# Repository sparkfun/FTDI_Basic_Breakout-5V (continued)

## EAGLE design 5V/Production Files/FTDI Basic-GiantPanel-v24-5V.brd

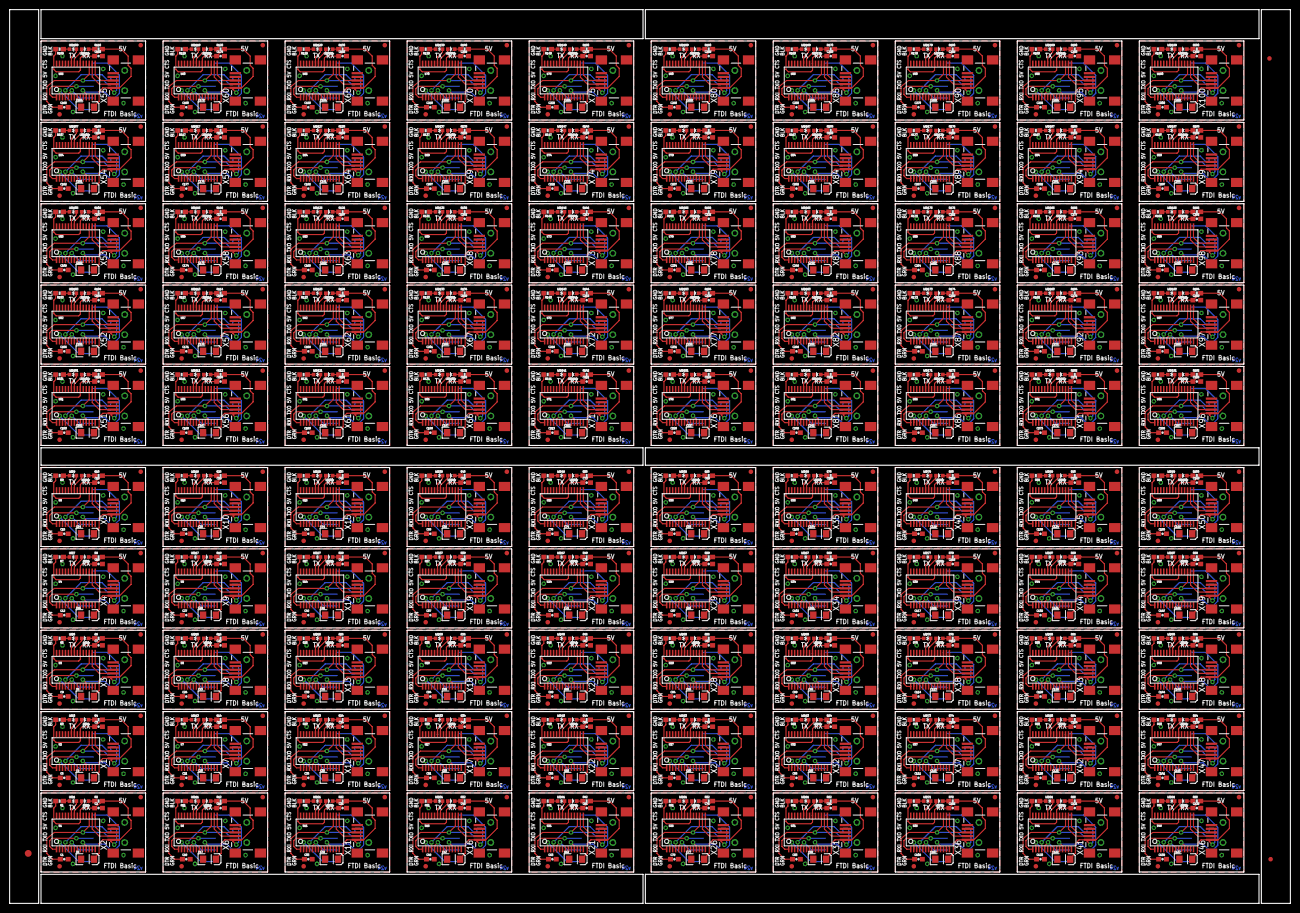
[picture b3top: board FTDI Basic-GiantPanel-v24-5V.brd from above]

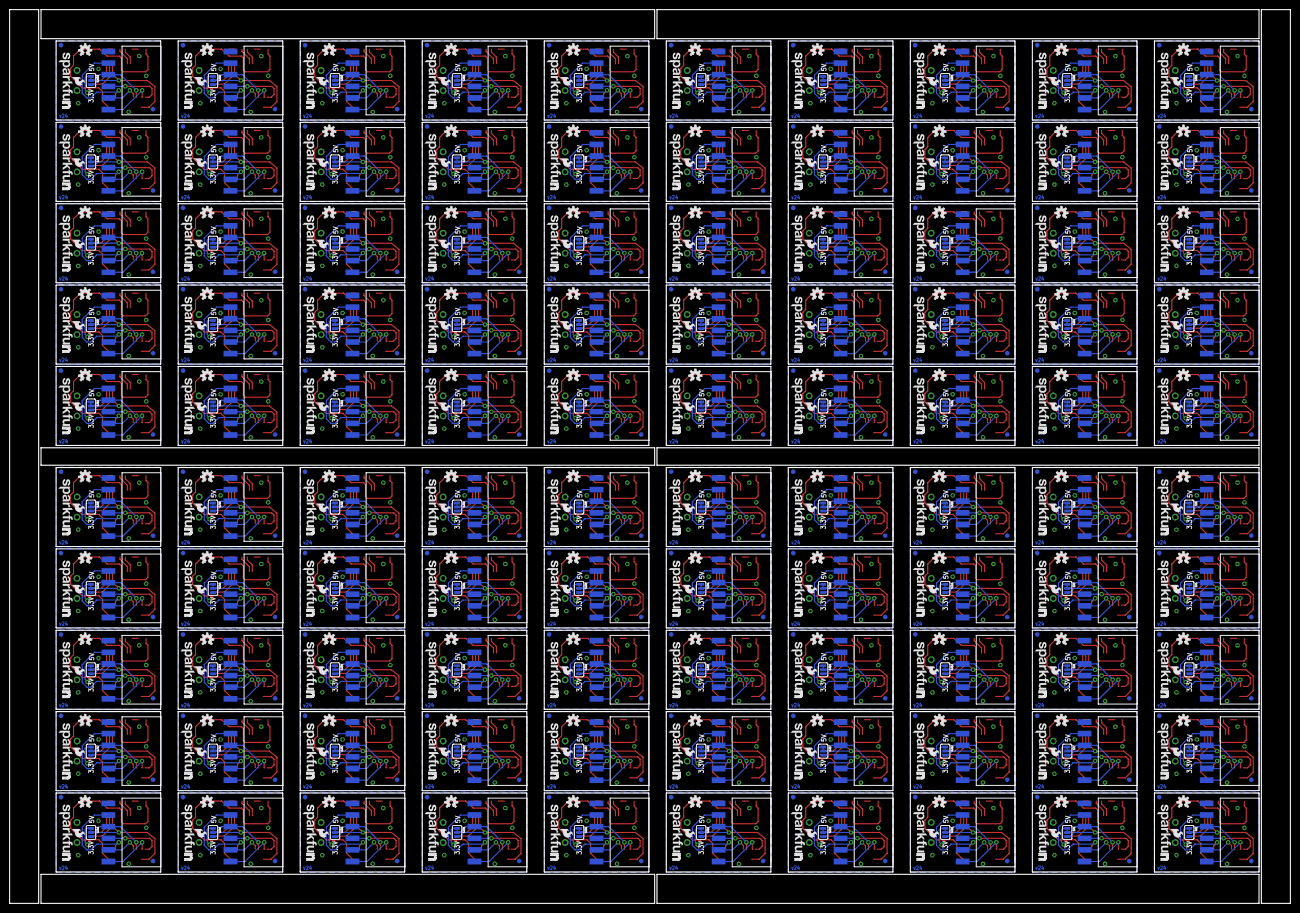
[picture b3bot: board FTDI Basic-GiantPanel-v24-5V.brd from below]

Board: 2 copper layers, 279.9 x 195.3 mm, 1803 parts (700 on the bottom side), 1400 nets.

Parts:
C1, C2, C3, C6, C7, C9, C10, C12, C13, C15, C16, C18, C19, C21, C22, C24, C25, C27, C28, C30, C31, C33, C34, C36, C37, C39, C40, C42, C43, C45, C46, C48, C49, C51, C52, C54, C55, C57, C58, C60, C61, C63, C64, C66, C67, C69, C70, C72, C73, C75, C76, C78, C79, C81, C82, C84, C85, C87, C88, C90, C91, C93, C94, C96, C97, C99, C100, C102, C103, C105, C106, C108, C109, C111, C112, C114, C115, C117, C118, C120, C121, C123, C124, C126, C127, C129, C130, C132, C133, C135, C136, C138, C139, C141, C142, C144, C145, C147, C148, C150, C151, C153, C154, C156, C157, C159, C160, C162, C163, C165, C166, C168, C169, C171, C172, C174, C175, C177, C178, C180, C181, C183, C184, C186, C187, C189, C190, C192, C193, C195, C196, C198, C199, C201, C202, C204, C205, C207, C208, C210, C211, C213, C214, C216, C217, C219, C220, C222, C223, C225, C226, C228, C229, C231, C232, C234, C235, C237, C238, C240, C241, C243, C244, C246, C247, C249, C250, C252, C253, C255, C256, C258, C259, C261, C262, C264, C265, C267, C268, C270, C271, C273, C274, C276, C277, C279, C280, C282, C283, C285, C286, C288, C289, C291, C292, C294, C295, C297, C298, C300: 0.1uF; 0603-CAP
C4, C5, C8, C11, C14, C17, C20, C23, C26, C29, C32, C35, C38, C41, C44, C47, C50, C53, C56, C59, C62, C65, C68, C71, C74, C77, C80, C83, C86, C89, C92, C95, C98, C101, C104, C107, C110, C113, C116, C119, C122, C125, C128, C131, C134, C137, C140, C143, C146, C149, C152, C155, C158, C161, C164, C167, C170, C173, C176, C179, C182, C185, C188, C191, C194, C197, C200, C203, C206, C209, C212, C215, C218, C221, C224, C227, C230, C233, C236, C239, C242, C245, C248, C251, C254, C257, C260, C263, C266, C269, C272, C275, C278, C281, C284, C287, C290, C293, C296, C299: 10uF; EIA3216
E$1: FIDUCIAL-1.5X3
E$6, E$16: FIDUCIAL-1X2
JP1, JP8, JP14, JP20, JP26, JP32, JP38, JP44, JP50, JP56, JP62, JP68, JP74, JP80, JP86, JP92, JP98, JP104, JP110, JP116, JP122, JP128, JP134, JP140, JP146, JP152, JP158, JP164, JP170, JP176, JP182, JP188, JP194, JP200, JP206, JP212, JP218, JP224, JP230, JP236, JP242, JP248, JP254, JP260, JP266, JP272, JP278, JP284, JP290, JP296, JP302, JP308, JP314, JP320, JP326, JP332, JP338, JP344, JP350, JP356, JP362, JP368, JP374, JP380, JP386, JP392, JP398, JP404, JP410, JP416, JP422, JP428, JP434, JP440, JP446, JP452, JP458, JP464, JP470, JP476, JP482, JP488, JP494, JP500, JP506, JP512, JP518, JP524, JP530, JP536, JP542, JP548, JP554, JP560, JP566, JP572, JP578, JP584, JP590, JP596: 1X06-SMD-FEMALE-V2
JP2, JP7, JP13, JP19, JP25, JP31, JP37, JP43, JP49, JP55, JP61, JP67, JP73, JP79, JP85, JP91, JP97, JP103, JP109, JP115, JP121, JP127, JP133, JP139, JP145, JP151, JP157, JP163, JP169, JP175, JP181, JP187, JP193, JP199, JP205, JP211, JP217, JP223, JP229, JP235, JP241, JP247, JP253, JP259, JP265, JP271, JP277, JP283, JP289, JP295, JP301, JP307, JP313, JP319, JP325, JP331, JP337, JP343, JP349, JP355, JP361, JP367, JP373, JP379, JP385, JP391, JP397, JP403, JP409, JP415, JP421, JP427, JP433, JP439, JP445, JP451, JP457, JP463, JP469, JP475, JP481, JP487, JP493, JP499, JP505, JP511, JP517, JP523, JP529, JP535, JP541, JP547, JP553, JP559, JP565, JP571, JP577, JP583, JP589, JP595: LOGO-SFESK; SFE-LOGO-FLAME
JP3, JP4, JP5, JP6, JP9, JP10, JP11, JP12, JP15, JP16, JP17, JP18, JP21, JP22, JP23, JP24, JP27, JP28, JP29, JP30, JP33, JP34, JP35, JP36, JP39, JP40, JP41, JP42, JP45, JP46, JP47, JP48, JP51, JP52, JP53, JP54, JP57, JP58, JP59, JP60, JP63, JP64, JP65, JP66, JP69, JP70, JP71, JP72, JP75, JP76, JP77, JP78, JP81, JP82, JP83, JP84, JP87, JP88, JP89, JP90, JP93, JP94, JP95, JP96, JP99, JP100, JP101, JP102, JP105, JP106, JP107, JP108, JP111, JP112, JP113, JP114, JP117, JP118, JP119, JP120, JP123, JP124, JP125, JP126, JP129, JP130, JP131, JP132, JP135, JP136, JP137, JP138, JP141, JP142, JP143, JP144, JP147, JP148, JP149, JP150, JP153, JP154, JP155, JP156, JP159, JP160, JP161, JP162, JP165, JP166, JP167, JP168, JP171, JP172, JP173, JP174, JP177, JP178, JP179, JP180, JP183, JP184, JP185, JP186, JP189, JP190, JP191, JP192, JP195, JP196, JP197, JP198, JP201, JP202, JP203, JP204, JP207, JP208, JP209, JP210, JP213, JP214, JP215, JP216, JP219, JP220, JP221, JP222, JP225, JP226, JP227, JP228, JP231, JP232, JP233, JP234, JP237, JP238, JP239, JP240, JP243, JP244, JP245, JP246, JP249, JP250, JP251, JP252, JP255, JP256, JP257, JP258, JP261, JP262, JP263, JP264, JP267, JP268, JP269, JP270, JP273, JP274, JP275, JP276, JP279, JP280, JP281, JP282, JP285, JP286, JP287, JP288, JP291, JP292, JP293, JP294, JP297, JP298, JP299, JP300, JP303, JP304, JP305, JP306, JP309, JP310, JP311, JP312, JP315, JP316, JP317, JP318, JP321, JP322, JP323, JP324, JP327, JP328, JP329, JP330, JP333, JP334, JP335, JP336, JP339, JP340, JP341, JP342, JP345, JP346, JP347, JP348, JP351, JP352, JP353, JP354, JP357, JP358, JP359, JP360, JP363, JP364, JP365, JP366, JP369, JP370, JP371, JP372, JP375, JP376, JP377, JP378, JP381, JP382, JP383, JP384, JP387, JP388, JP389, JP390, JP393, JP394, JP395, JP396, JP399, JP400, JP401, JP402, JP405, JP406, JP407, JP408, JP411, JP412, JP413, JP414, JP417, JP418, JP419, JP420, JP423, JP424, JP425, JP426, JP429, JP430, JP431, JP432, JP435, JP436, JP437, JP438, JP441, JP442, JP443, JP444, JP447, JP448, JP449, JP450, JP453, JP454, JP455, JP456, JP459, JP460, JP461, JP462, JP465, JP466, JP467, JP468, JP471, JP472, JP473, JP474, JP477, JP478, JP479, JP480, JP483, JP484, JP485, JP486, JP489, JP490, JP491, JP492, JP495, JP496, JP497, JP498, JP501, JP502, JP503, JP504, JP507, JP508, JP509, JP510, JP513, JP514, JP515, JP516, JP519, JP520, JP521, JP522, JP525, JP526, JP527, JP528, JP531, JP532, JP533, JP534, JP537, JP538, JP539, JP540, JP543, JP544, JP545, JP546, JP549, JP550, JP551, JP552, JP555, JP556, JP557, JP558, JP561, JP562, JP563, JP564, JP567, JP568, JP569, JP570, JP573, JP574, JP575, JP576, JP579, JP580, JP581, JP582, JP585, JP586, JP587, JP588, JP591, JP592, JP593, JP594, JP597, JP598, JP599, JP600: FIDUCIAL1X2; FIDUCIAL-1X2
LED1, LED3, LED5, LED7, LED9, LED11, LED13, LED15, LED17, LED19, LED21, LED23, LED25, LED27, LED29, LED31, LED33, LED35, LED37, LED39, LED41, LED43, LED45, LED47, LED49, LED51, LED53, LED55, LED57, LED59, LED61, LED63, LED65, LED67, LED69, LED71, LED73, LED75, LED77, LED79, LED81, LED83, LED85, LED87, LED89, LED91, LED93, LED95, LED97, LED99, LED101, LED103, LED105, LED107, LED109, LED111, LED113, LED115, LED117, LED119, LED121, LED123, LED125, LED127, LED129, LED131, LED133, LED135, LED137, LED139, LED141, LED143, LED145, LED147, LED149, LED151, LED153, LED155, LED157, LED159, LED161, LED163, LED165, LED167, LED169, LED171, LED173, LED175, LED177, LED179, LED181, LED183, LED185, LED187, LED189, LED191, LED193, LED195, LED197, LED199: Red; LED-0603
LED2, LED4, LED6, LED8, LED10, LED12, LED14, LED16, LED18, LED20, LED22, LED24, LED26, LED28, LED30, LED32, LED34, LED36, LED38, LED40, LED42, LED44, LED46, LED48, LED50, LED52, LED54, LED56, LED58, LED60, LED62, LED64, LED66, LED68, LED70, LED72, LED74, LED76, LED78, LED80, LED82, LED84, LED86, LED88, LED90, LED92, LED94, LED96, LED98, LED100, LED102, LED104, LED106, LED108, LED110, LED112, LED114, LED116, LED118, LED120, LED122, LED124, LED126, LED128, LED130, LED132, LED134, LED136, LED138, LED140, LED142, LED144, LED146, LED148, LED150, LED152, LED154, LED156, LED158, LED160, LED162, LED164, LED166, LED168, LED170, LED172, LED174, LED176, LED178, LED180, LED182, LED184, LED186, LED188, LED190, LED192, LED194, LED196, LED198, LED200: Green; LED-0603
LOGO1, LOGO2, LOGO3, LOGO4, LOGO5, LOGO6, LOGO7, LOGO8, LOGO9, LOGO10, LOGO11, LOGO12, LOGO13, LOGO14, LOGO15, LOGO16, LOGO17, LOGO18, LOGO19, LOGO20, LOGO21, LOGO22, LOGO23, LOGO24, LOGO25, LOGO26, LOGO27, LOGO28, LOGO29, LOGO30, LOGO31, LOGO32, LOGO33, LOGO34, LOGO35, LOGO36, LOGO37, LOGO38, LOGO39, LOGO40, LOGO41, LOGO42, LOGO43, LOGO44, LOGO45, LOGO46, LOGO47, LOGO48, LOGO49, LOGO50, LOGO51, LOGO52, LOGO53, LOGO54, LOGO55, LOGO56, LOGO57, LOGO58, LOGO59, LOGO60, LOGO61, LOGO62, LOGO63, LOGO64, LOGO65, LOGO66, LOGO67, LOGO68, LOGO69, LOGO70, LOGO71, LOGO72, LOGO73, LOGO74, LOGO75, LOGO76, LOGO77, LOGO78, LOGO79, LOGO80, LOGO81, LOGO82, LOGO83, LOGO84, LOGO85, LOGO86, LOGO87, LOGO88, LOGO89, LOGO90, LOGO91, LOGO92, LOGO93, LOGO94, LOGO95, LOGO96, LOGO97, LOGO98, LOGO99, LOGO100: OSHW-LOGOS; OSHW-LOGO-S
R1, R2, R3, R4, R5, R6, R7, R8, R9, R10, R11, R12, R13, R14, R15, R16, R17, R18, R19, R20, R21, R22, R23, R24, R25, R26, R27, R28, R29, R30, R31, R32, R33, R34, R35, R36, R37, R38, R39, R40, R41, R42, R43, R44, R45, R46, R47, R48, R49, R50, R51, R52, R53, R54, R55, R56, R57, R58, R59, R60, R61, R62, R63, R64, R65, R66, R67, R68, R69, R70, R71, R72, R73, R74, R75, R76, R77, R78, R79, R80, R81, R82, R83, R84, R85, R86, R87, R88, R89, R90, R91, R92, R93, R94, R95, R96, R97, R98, R99, R100, R101, R102, R103, R104, R105, R106, R107, R108, R109, R110, R111, R112, R113, R114, R115, R116, R117, R118, R119, R120, R121, R122, R123, R124, R125, R126, R127, R128, R129, R130, R131, R132, R133, R134, R135, R136, R137, R138, R139, R140, R141, R142, R143, R144, R145, R146, R147, R148, R149, R150, R151, R152, R153, R154, R155, R156, R157, R158, R159, R160, R161, R162, R163, R164, R165, R166, R167, R168, R169, R170, R171, R172, R173, R174, R175, R176, R177, R178, R179, R180, R181, R182, R183, R184, R185, R186, R187, R188, R189, R190, R191, R192, R193, R194, R195, R196, R197, R198, R199, R200: 1K; 0603-RES
SJ1, SJ2, SJ3, SJ4, SJ5, SJ6, SJ7, SJ8, SJ9, SJ10, SJ11, SJ12, SJ13, SJ14, SJ15, SJ16, SJ17, SJ18, SJ19, SJ20, SJ21, SJ22, SJ23, SJ24, SJ25, SJ26, SJ27, SJ28, SJ29, SJ30, SJ31, SJ32, SJ33, SJ34, SJ35, SJ36, SJ37, SJ38, SJ39, SJ40, SJ41, SJ42, SJ43, SJ44, SJ45, SJ46, SJ47, SJ48, SJ49, SJ50, SJ51, SJ52, SJ53, SJ54, SJ55, SJ56, SJ57, SJ58, SJ59, SJ60, SJ61, SJ62, SJ63, SJ64, SJ65, SJ66, SJ67, SJ68, SJ69, SJ70, SJ71, SJ72, SJ73, SJ74, SJ75, SJ76, SJ77, SJ78, SJ79, SJ80, SJ81, SJ82, SJ83, SJ84, SJ85, SJ86, SJ87, SJ88, SJ89, SJ90, SJ91, SJ92, SJ93, SJ94, SJ95, SJ96, SJ97, SJ98, SJ99, SJ100: SJ_3
U1, U2, U3, U4, U5, U6, U7, U8, U9, U10, U11, U12, U13, U14, U15, U16, U17, U18, U19, U20, U21, U22, U23, U24, U25, U26, U27, U28, U29, U30, U31, U32, U33, U34, U35, U36, U37, U38, U39, U40, U41, U42, U43, U44, U45, U46, U47, U48, U49, U50, U51, U52, U53, U54, U55, U56, U57, U58, U59, U60, U61, U62, U63, U64, U65, U66, U67, U68, U69, U70, U71, U72, U73, U74, U75, U76, U77, U78, U79, U80, U81, U82, U83, U84, U85, U86, U87, U88, U89, U90, U91, U92, U93, U94, U95, U96, U97, U98, U99, U100: FT232RLSSOP; SSOP28DB
U$1, U$2, U$3, U$4, U$5, U$6, U$7, U$8, U$9, U$10, U$11, U$12, U$13, U$14, U$15, U$16, U$17, U$18, U$19, U$20, U$21, U$22, U$23, U$24, U$25, U$26, U$27, U$28, U$29, U$30, U$31, U$32, U$33, U$34, U$35, U$36, U$37, U$38, U$39, U$40, U$41, U$42, U$43, U$44, U$45, U$46, U$47, U$48, U$49, U$50, U$51, U$52, U$53, U$54, U$55, U$56, U$57, U$58, U$59, U$60, U$61, U$62, U$63, U$64, U$65, U$66, U$67, U$68, U$69, U$70, U$71, U$72, U$73, U$74, U$75, U$76, U$77, U$78, U$79, U$80, U$81, U$82, U$83, U$84, U$85, U$86, U$87, U$88, U$89, U$90, U$91, U$92, U$93, U$94, U$95, U$96, U$97, U$98, U$99, U$100: LOGO-SFENW2; SFE-NEW-WEB
X1, X2, X3, X4, X5, X6, X7, X8, X9, X10, X11, X12, X13, X14, X15, X16, X17, X18, X19, X20, X21, X22, X23, X24, X25, X26, X27, X28, X29, X30, X31, X32, X33, X34, X35, X36, X37, X38, X39, X40, X41, X42, X43, X44, X45, X46, X47, X48, X49, X50, X51, X52, X53, X54, X55, X56, X57, X58, X59, X60, X61, X62, X63, X64, X65, X66, X67, X68, X69, X70, X71, X72, X73, X74, X75, X76, X77, X78, X79, X80, X81, X82, X83, X84, X85, X86, X87, X88, X89, X90, X91, X92, X93, X94, X95, X96, X97, X98, X99, X100: USB-SMD-NS; USB-MINIB-NOSTOP

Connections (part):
3.3V: C1.1, SJ2.3, U1.17
3.3V1: C6.1, SJ1.3, U2.17
3.3V2: C9.1, SJ3.3, U3.17
3.3V3: C12.1, SJ4.3, U4.17
3.3V4: C15.1, SJ5.3, U5.17
3.3V5: C18.1, SJ6.3, U6.17
3.3V6: C21.1, SJ7.3, U7.17
3.3V7: C24.1, SJ8.3, U8.17
3.3V8: C27.1, SJ9.3, U9.17
3.3V9: C30.1, SJ10.3, U10.17
3.3V10: C33.1, SJ11.3, U11.17
3.3V11: C36.1, SJ12.3, U12.17
3.3V12: C39.1, SJ13.3, U13.17
3.3V13: C42.1, SJ14.3, U14.17
3.3V14: C45.1, SJ15.3, U15.17
3.3V15: C48.1, SJ16.3, U16.17
3.3V16: C51.1, SJ17.3, U17.17
3.3V17: C54.1, SJ18.3, U18.17
3.3V18: C57.1, SJ19.3, U19.17
3.3V19: C60.1, SJ20.3, U20.17
3.3V20: C63.1, SJ21.3, U21.17
3.3V21: C66.1, SJ22.3, U22.17
3.3V22: C69.1, SJ23.3, U23.17
3.3V23: C72.1, SJ24.3, U24.17
3.3V24: C75.1, SJ25.3, U25.17
3.3V25: C78.1, SJ26.3, U26.17
3.3V26: C81.1, SJ27.3, U27.17
3.3V27: C84.1, SJ28.3, U28.17
3.3V28: C87.1, SJ29.3, U29.17
3.3V29: C90.1, SJ30.3, U30.17
3.3V30: C93.1, SJ31.3, U31.17
3.3V31: C96.1, SJ32.3, U32.17
3.3V32: C99.1, SJ33.3, U33.17
3.3V33: C102.1, SJ34.3, U34.17
3.3V34: C105.1, SJ35.3, U35.17
3.3V35: C108.1, SJ36.3, U36.17
3.3V36: C111.1, SJ37.3, U37.17
3.3V37: C114.1, SJ38.3, U38.17
3.3V38: C117.1, SJ39.3, U39.17
3.3V39: C120.1, SJ40.3, U40.17
3.3V40: C123.1, SJ41.3, U41.17
3.3V41: C126.1, SJ42.3, U42.17
3.3V42: C129.1, SJ43.3, U43.17
3.3V43: C132.1, SJ44.3, U44.17
3.3V44: C135.1, SJ45.3, U45.17
3.3V45: C138.1, SJ46.3, U46.17
3.3V46: C141.1, SJ47.3, U47.17
3.3V47: C144.1, SJ48.3, U48.17
3.3V48: C147.1, SJ49.3, U49.17
3.3V49: C150.1, SJ50.3, U50.17
3.3V50: C153.1, SJ51.3, U51.17
3.3V51: C156.1, SJ52.3, U52.17
3.3V52: C159.1, SJ53.3, U53.17
3.3V53: C162.1, SJ54.3, U54.17
3.3V54: C165.1, SJ55.3, U55.17
3.3V55: C168.1, SJ56.3, U56.17
3.3V56: C171.1, SJ57.3, U57.17
3.3V57: C174.1, SJ58.3, U58.17
3.3V58: C177.1, SJ59.3, U59.17
3.3V59: C180.1, SJ60.3, U60.17
3.3V60: C183.1, SJ61.3, U61.17
3.3V61: C186.1, SJ62.3, U62.17
3.3V62: C189.1, SJ63.3, U63.17
3.3V63: C192.1, SJ64.3, U64.17
3.3V64: C195.1, SJ65.3, U65.17
3.3V65: C198.1, SJ66.3, U66.17
3.3V66: C201.1, SJ67.3, U67.17
3.3V67: C204.1, SJ68.3, U68.17
3.3V68: C207.1, SJ69.3, U69.17
3.3V69: C210.1, SJ70.3, U70.17
3.3V70: C213.1, SJ71.3, U71.17
3.3V71: C216.1, SJ72.3, U72.17
3.3V72: C219.1, SJ73.3, U73.17
3.3V73: C222.1, SJ74.3, U74.17
3.3V74: C225.1, SJ75.3, U75.17
3.3V75: C228.1, SJ76.3, U76.17
3.3V76: C231.1, SJ77.3, U77.17
3.3V77: C234.1, SJ78.3, U78.17
3.3V78: C237.1, SJ79.3, U79.17
3.3V79: C240.1, SJ80.3, U80.17
3.3V80: C243.1, SJ81.3, U81.17
3.3V81: C246.1, SJ82.3, U82.17
3.3V82: C249.1, SJ83.3, U83.17
3.3V83: C252.1, SJ84.3, U84.17
3.3V84: C255.1, SJ85.3, U85.17
3.3V85: C258.1, SJ86.3, U86.17
3.3V86: C261.1, SJ87.3, U87.17
3.3V87: C264.1, SJ88.3, U88.17
3.3V88: C267.1, SJ89.3, U89.17
3.3V89: C270.1, SJ90.3, U90.17
3.3V90: C273.1, SJ91.3, U91.17
3.3V91: C276.1, SJ92.3, U92.17
3.3V92: C279.1, SJ93.3, U93.17
3.3V93: C282.1, SJ94.3, U94.17
3.3V94: C285.1, SJ95.3, U95.17
3.3V95: C288.1, SJ96.3, U96.17
3.3V96: C291.1, SJ97.3, U97.17
3.3V97: C294.1, SJ98.3, U98.17
3.3V98: C297.1, SJ99.3, U99.17
3.3V99: C300.1, SJ100.3, U100.17
5V: C2.1, C5.A, R1.2, R2.2, SJ2.1, U1.20, X2.VBUS
5V1: C3.1, C4.A, R3.2, R4.2, SJ1.1, U2.20, X1.VBUS
5V2: C7.1, C8.A, R5.2, R6.2, SJ3.1, U3.20, X3.VBUS
5V3: C10.1, C11.A, R7.2, R8.2, SJ4.1, U4.20, X4.VBUS
5V4: C13.1, C14.A, R9.2, R10.2, SJ5.1, U5.20, X5.VBUS
5V5: C16.1, C17.A, R11.2, R12.2, SJ6.1, U6.20, X6.VBUS
5V6: C19.1, C20.A, R13.2, R14.2, SJ7.1, U7.20, X7.VBUS
5V7: C22.1, C23.A, R15.2, R16.2, SJ8.1, U8.20, X8.VBUS
5V8: C25.1, C26.A, R17.2, R18.2, SJ9.1, U9.20, X9.VBUS
5V9: C28.1, C29.A, R19.2, R20.2, SJ10.1, U10.20, X10.VBUS
5V10: C31.1, C32.A, R21.2, R22.2, SJ11.1, U11.20, X11.VBUS
5V11: C34.1, C35.A, R23.2, R24.2, SJ12.1, U12.20, X12.VBUS
5V12: C37.1, C38.A, R25.2, R26.2, SJ13.1, U13.20, X13.VBUS
5V13: C40.1, C41.A, R27.2, R28.2, SJ14.1, U14.20, X14.VBUS
5V14: C43.1, C44.A, R29.2, R30.2, SJ15.1, U15.20, X15.VBUS
5V15: C46.1, C47.A, R31.2, R32.2, SJ16.1, U16.20, X16.VBUS
5V16: C49.1, C50.A, R33.2, R34.2, SJ17.1, U17.20, X17.VBUS
5V17: C52.1, C53.A, R35.2, R36.2, SJ18.1, U18.20, X18.VBUS
5V18: C55.1, C56.A, R37.2, R38.2, SJ19.1, U19.20, X19.VBUS
5V19: C58.1, C59.A, R39.2, R40.2, SJ20.1, U20.20, X20.VBUS
5V20: C61.1, C62.A, R41.2, R42.2, SJ21.1, U21.20, X21.VBUS
5V21: C64.1, C65.A, R43.2, R44.2, SJ22.1, U22.20, X22.VBUS
5V22: C67.1, C68.A, R45.2, R46.2, SJ23.1, U23.20, X23.VBUS
5V23: C70.1, C71.A, R47.2, R48.2, SJ24.1, U24.20, X24.VBUS
5V24: C73.1, C74.A, R49.2, R50.2, SJ25.1, U25.20, X25.VBUS
5V25: C76.1, C77.A, R51.2, R52.2, SJ26.1, U26.20, X26.VBUS
5V26: C79.1, C80.A, R53.2, R54.2, SJ27.1, U27.20, X27.VBUS
5V27: C82.1, C83.A, R55.2, R56.2, SJ28.1, U28.20, X28.VBUS
5V28: C85.1, C86.A, R57.2, R58.2, SJ29.1, U29.20, X29.VBUS
5V29: C88.1, C89.A, R59.2, R60.2, SJ30.1, U30.20, X30.VBUS
5V30: C91.1, C92.A, R61.2, R62.2, SJ31.1, U31.20, X31.VBUS
5V31: C94.1, C95.A, R63.2, R64.2, SJ32.1, U32.20, X32.VBUS
5V32: C97.1, C98.A, R65.2, R66.2, SJ33.1, U33.20, X33.VBUS
5V33: C100.1, C101.A, R67.2, R68.2, SJ34.1, U34.20, X34.VBUS
5V34: C103.1, C104.A, R69.2, R70.2, SJ35.1, U35.20, X35.VBUS
5V35: C106.1, C107.A, R71.2, R72.2, SJ36.1, U36.20, X36.VBUS
5V36: C109.1, C110.A, R73.2, R74.2, SJ37.1, U37.20, X37.VBUS
5V37: C112.1, C113.A, R75.2, R76.2, SJ38.1, U38.20, X38.VBUS
5V38: C115.1, C116.A, R77.2, R78.2, SJ39.1, U39.20, X39.VBUS
5V39: C118.1, C119.A, R79.2, R80.2, SJ40.1, U40.20, X40.VBUS
5V40: C121.1, C122.A, R81.2, R82.2, SJ41.1, U41.20, X41.VBUS
5V41: C124.1, C125.A, R83.2, R84.2, SJ42.1, U42.20, X42.VBUS
5V42: C127.1, C128.A, R85.2, R86.2, SJ43.1, U43.20, X43.VBUS
5V43: C130.1, C131.A, R87.2, R88.2, SJ44.1, U44.20, X44.VBUS
5V44: C133.1, C134.A, R89.2, R90.2, SJ45.1, U45.20, X45.VBUS
5V45: C136.1, C137.A, R91.2, R92.2, SJ46.1, U46.20, X46.VBUS
5V46: C139.1, C140.A, R93.2, R94.2, SJ47.1, U47.20, X47.VBUS
5V47: C142.1, C143.A, R95.2, R96.2, SJ48.1, U48.20, X48.VBUS
5V48: C145.1, C146.A, R97.2, R98.2, SJ49.1, U49.20, X49.VBUS
5V49: C148.1, C149.A, R99.2, R100.2, SJ50.1, U50.20, X50.VBUS
5V50: C151.1, C152.A, R101.2, R102.2, SJ51.1, U51.20, X51.VBUS
5V51: C154.1, C155.A, R103.2, R104.2, SJ52.1, U52.20, X52.VBUS
5V52: C157.1, C158.A, R105.2, R106.2, SJ53.1, U53.20, X53.VBUS
5V53: C160.1, C161.A, R107.2, R108.2, SJ54.1, U54.20, X54.VBUS
5V54: C163.1, C164.A, R109.2, R110.2, SJ55.1, U55.20, X55.VBUS
5V55: C166.1, C167.A, R111.2, R112.2, SJ56.1, U56.20, X56.VBUS
5V56: C169.1, C170.A, R113.2, R114.2, SJ57.1, U57.20, X57.VBUS
5V57: C172.1, C173.A, R115.2, R116.2, SJ58.1, U58.20, X58.VBUS
5V58: C175.1, C176.A, R117.2, R118.2, SJ59.1, U59.20, X59.VBUS
5V59: C178.1, C179.A, R119.2, R120.2, SJ60.1, U60.20, X60.VBUS
5V60: C181.1, C182.A, R121.2, R122.2, SJ61.1, U61.20, X61.VBUS
5V61: C184.1, C185.A, R123.2, R124.2, SJ62.1, U62.20, X62.VBUS
5V62: C187.1, C188.A, R125.2, R126.2, SJ63.1, U63.20, X63.VBUS
5V63: C190.1, C191.A, R127.2, R128.2, SJ64.1, U64.20, X64.VBUS
5V64: C193.1, C194.A, R129.2, R130.2, SJ65.1, U65.20, X65.VBUS
5V65: C196.1, C197.A, R131.2, R132.2, SJ66.1, U66.20, X66.VBUS
5V66: C199.1, C200.A, R133.2, R134.2, SJ67.1, U67.20, X67.VBUS
5V67: C202.1, C203.A, R135.2, R136.2, SJ68.1, U68.20, X68.VBUS
5V68: C205.1, C206.A, R137.2, R138.2, SJ69.1, U69.20, X69.VBUS
5V69: C208.1, C209.A, R139.2, R140.2, SJ70.1, U70.20, X70.VBUS
5V70: C211.1, C212.A, R141.2, R142.2, SJ71.1, U71.20, X71.VBUS
5V71: C214.1, C215.A, R143.2, R144.2, SJ72.1, U72.20, X72.VBUS
5V72: C217.1, C218.A, R145.2, R146.2, SJ73.1, U73.20, X73.VBUS
5V73: C220.1, C221.A, R147.2, R148.2, SJ74.1, U74.20, X74.VBUS
5V74: C223.1, C224.A, R149.2, R150.2, SJ75.1, U75.20, X75.VBUS
5V75: C226.1, C227.A, R151.2, R152.2, SJ76.1, U76.20, X76.VBUS
5V76: C229.1, C230.A, R153.2, R154.2, SJ77.1, U77.20, X77.VBUS
5V77: C232.1, C233.A, R155.2, R156.2, SJ78.1, U78.20, X78.VBUS
5V78: C235.1, C236.A, R157.2, R158.2, SJ79.1, U79.20, X79.VBUS
5V79: C238.1, C239.A, R159.2, R160.2, SJ80.1, U80.20, X80.VBUS
5V80: C241.1, C242.A, R161.2, R162.2, SJ81.1, U81.20, X81.VBUS
5V81: C244.1, C245.A, R163.2, R164.2, SJ82.1, U82.20, X82.VBUS
5V82: C247.1, C248.A, R165.2, R166.2, SJ83.1, U83.20, X83.VBUS
5V83: C250.1, C251.A, R167.2, R168.2, SJ84.1, U84.20, X84.VBUS
5V84: C253.1, C254.A, R169.2, R170.2, SJ85.1, U85.20, X85.VBUS
5V85: C256.1, C257.A, R171.2, R172.2, SJ86.1, U86.20, X86.VBUS
5V86: C259.1, C260.A, R173.2, R174.2, SJ87.1, U87.20, X87.VBUS
5V87: C262.1, C263.A, R175.2, R176.2, SJ88.1, U88.20, X88.VBUS
5V88: C265.1, C266.A, R177.2, R178.2, SJ89.1, U89.20, X89.VBUS
5V89: C268.1, C269.A, R179.2, R180.2, SJ90.1, U90.20, X90.VBUS
5V90: C271.1, C272.A, R181.2, R182.2, SJ91.1, U91.20, X91.VBUS
5V91: C274.1, C275.A, R183.2, R184.2, SJ92.1, U92.20, X92.VBUS
5V92: C277.1, C278.A, R185.2, R186.2, SJ93.1, U93.20, X93.VBUS
5V93: C280.1, C281.A, R187.2, R188.2, SJ94.1, U94.20, X94.VBUS
5V94: C283.1, C284.A, R189.2, R190.2, SJ95.1, U95.20, X95.VBUS
5V95: C286.1, C287.A, R191.2, R192.2, SJ96.1, U96.20, X96.VBUS
5V96: C289.1, C290.A, R193.2, R194.2, SJ97.1, U97.20, X97.VBUS
5V97: C292.1, C293.A, R195.2, R196.2, SJ98.1, U98.20, X98.VBUS
5V98: C295.1, C296.A, R197.2, R198.2, SJ99.1, U99.20, X99.VBUS
5V99: C298.1, C299.A, R199.2, R200.2, SJ100.1, U100.20, X100.VBUS
CTS: JP1.2, U1.11
CTS1: JP8.2, U2.11
CTS2: JP14.2, U3.11
CTS3: JP20.2, U4.11
CTS4: JP26.2, U5.11
CTS5: JP32.2, U6.11
CTS6: JP38.2, U7.11
CTS7: JP44.2, U8.11
CTS8: JP50.2, U9.11
CTS9: JP56.2, U10.11
CTS10: JP62.2, U11.11
CTS11: JP68.2, U12.11
CTS12: JP74.2, U13.11
CTS13: JP80.2, U14.11
CTS14: JP86.2, U15.11
CTS15: JP92.2, U16.11
CTS16: JP98.2, U17.11
CTS17: JP104.2, U18.11
CTS18: JP110.2, U19.11
CTS19: JP116.2, U20.11
CTS20: JP122.2, U21.11
CTS21: JP128.2, U22.11
CTS22: JP134.2, U23.11
CTS23: JP140.2, U24.11
CTS24: JP146.2, U25.11
CTS25: JP152.2, U26.11
CTS26: JP158.2, U27.11
CTS27: JP164.2, U28.11
CTS28: JP170.2, U29.11
CTS29: JP176.2, U30.11
CTS30: JP182.2, U31.11
CTS31: JP188.2, U32.11
CTS32: JP194.2, U33.11
CTS33: JP200.2, U34.11
CTS34: JP206.2, U35.11
CTS35: JP212.2, U36.11
CTS36: JP218.2, U37.11
CTS37: JP224.2, U38.11
CTS38: JP230.2, U39.11
CTS39: JP236.2, U40.11
CTS40: JP242.2, U41.11
CTS41: JP248.2, U42.11
CTS42: JP254.2, U43.11
CTS43: JP260.2, U44.11
CTS44: JP266.2, U45.11
CTS45: JP272.2, U46.11
CTS46: JP278.2, U47.11
CTS47: JP284.2, U48.11
CTS48: JP290.2, U49.11
CTS49: JP296.2, U50.11
CTS50: JP302.2, U51.11
CTS51: JP308.2, U52.11
CTS52: JP314.2, U53.11
CTS53: JP320.2, U54.11
CTS54: JP326.2, U55.11
CTS55: JP332.2, U56.11
CTS56: JP338.2, U57.11
CTS57: JP344.2, U58.11
CTS58: JP350.2, U59.11
CTS59: JP356.2, U60.11
CTS60: JP362.2, U61.11
CTS61: JP368.2, U62.11
CTS62: JP374.2, U63.11
CTS63: JP380.2, U64.11
CTS64: JP386.2, U65.11
CTS65: JP392.2, U66.11
CTS66: JP398.2, U67.11
CTS67: JP404.2, U68.11
CTS68: JP410.2, U69.11
CTS69: JP416.2, U70.11
CTS70: JP422.2, U71.11
CTS71: JP428.2, U72.11
CTS72: JP434.2, U73.11
CTS73: JP440.2, U74.11
CTS74: JP446.2, U75.11
CTS75: JP452.2, U76.11
CTS76: JP458.2, U77.11
CTS77: JP464.2, U78.11
CTS78: JP470.2, U79.11
CTS79: JP476.2, U80.11
CTS80: JP482.2, U81.11
CTS81: JP488.2, U82.11
CTS82: JP494.2, U83.11
CTS83: JP500.2, U84.11
CTS84: JP506.2, U85.11
CTS85: JP512.2, U86.11
CTS86: JP518.2, U87.11
CTS87: JP524.2, U88.11
CTS88: JP530.2, U89.11
CTS89: JP536.2, U90.11
CTS90: JP542.2, U91.11
CTS91: JP548.2, U92.11
CTS92: JP554.2, U93.11
CTS93: JP560.2, U94.11
CTS94: JP566.2, U95.11
CTS95: JP572.2, U96.11
CTS96: JP578.2, U97.11
CTS97: JP584.2, U98.11
CTS98: JP590.2, U99.11
CTS99: JP596.2, U100.11
DTR: JP1.6, U1.2
DTR1: JP8.6, U2.2
DTR2: JP14.6, U3.2
DTR3: JP20.6, U4.2
DTR4: JP26.6, U5.2
DTR5: JP32.6, U6.2
DTR6: JP38.6, U7.2
DTR7: JP44.6, U8.2
DTR8: JP50.6, U9.2
DTR9: JP56.6, U10.2
DTR10: JP62.6, U11.2
DTR11: JP68.6, U12.2
DTR12: JP74.6, U13.2
DTR13: JP80.6, U14.2
DTR14: JP86.6, U15.2
DTR15: JP92.6, U16.2
DTR16: JP98.6, U17.2
DTR17: JP104.6, U18.2
DTR18: JP110.6, U19.2
DTR19: JP116.6, U20.2
DTR20: JP122.6, U21.2
DTR21: JP128.6, U22.2
DTR22: JP134.6, U23.2
DTR23: JP140.6, U24.2
DTR24: JP146.6, U25.2
DTR25: JP152.6, U26.2
DTR26: JP158.6, U27.2
DTR27: JP164.6, U28.2
DTR28: JP170.6, U29.2
DTR29: JP176.6, U30.2
DTR30: JP182.6, U31.2
DTR31: JP188.6, U32.2
DTR32: JP194.6, U33.2
DTR33: JP200.6, U34.2
DTR34: JP206.6, U35.2
DTR35: JP212.6, U36.2
DTR36: JP218.6, U37.2
DTR37: JP224.6, U38.2
DTR38: JP230.6, U39.2
DTR39: JP236.6, U40.2
DTR40: JP242.6, U41.2
DTR41: JP248.6, U42.2
DTR42: JP254.6, U43.2
DTR43: JP260.6, U44.2
DTR44: JP266.6, U45.2
DTR45: JP272.6, U46.2
DTR46: JP278.6, U47.2
DTR47: JP284.6, U48.2
DTR48: JP290.6, U49.2
DTR49: JP296.6, U50.2
DTR50: JP302.6, U51.2
DTR51: JP308.6, U52.2
DTR52: JP314.6, U53.2
DTR53: JP320.6, U54.2
DTR54: JP326.6, U55.2
DTR55: JP332.6, U56.2
DTR56: JP338.6, U57.2
DTR57: JP344.6, U58.2
DTR58: JP350.6, U59.2
DTR59: JP356.6, U60.2
DTR60: JP362.6, U61.2
DTR61: JP368.6, U62.2
DTR62: JP374.6, U63.2
DTR63: JP380.6, U64.2
DTR64: JP386.6, U65.2
DTR65: JP392.6, U66.2
DTR66: JP398.6, U67.2
DTR67: JP404.6, U68.2
DTR68: JP410.6, U69.2
DTR69: JP416.6, U70.2
DTR70: JP422.6, U71.2
DTR71: JP428.6, U72.2
DTR72: JP434.6, U73.2
DTR73: JP440.6, U74.2
DTR74: JP446.6, U75.2
DTR75: JP452.6, U76.2
DTR76: JP458.6, U77.2
DTR77: JP464.6, U78.2
DTR78: JP470.6, U79.2
DTR79: JP476.6, U80.2
DTR80: JP482.6, U81.2
DTR81: JP488.6, U82.2
DTR82: JP494.6, U83.2
DTR83: JP500.6, U84.2
DTR84: JP506.6, U85.2
DTR85: JP512.6, U86.2
DTR86: JP518.6, U87.2
DTR87: JP524.6, U88.2
DTR88: JP530.6, U89.2
DTR89: JP536.6, U90.2
DTR90: JP542.6, U91.2
DTR91: JP548.6, U92.2
DTR92: JP554.6, U93.2
DTR93: JP560.6, U94.2
DTR94: JP566.6, U95.2
DTR95: JP572.6, U96.2
DTR96: JP578.6, U97.2
DTR97: JP584.6, U98.2
DTR98: JP590.6, U99.2
DTR99: JP596.6, U100.2
GND: C1.2, C2.2, C5.C, JP1.1, U1.7, U1.18, U1.21, U1.25, U1.26, X2.GND
GND1: C3.2, C4.C, C6.2, JP8.1, U2.7, U2.18, U2.21, U2.25, U2.26, X1.GND
GND2: C7.2, C8.C, C9.2, JP14.1, U3.7, U3.18, U3.21, U3.25, U3.26, X3.GND
GND3: C10.2, C11.C, C12.2, JP20.1, U4.7, U4.18, U4.21, U4.25, U4.26, X4.GND
GND4: C13.2, C14.C, C15.2, JP26.1, U5.7, U5.18, U5.21, U5.25, U5.26, X5.GND
GND5: C16.2, C17.C, C18.2, JP32.1, U6.7, U6.18, U6.21, U6.25, U6.26, X6.GND
GND6: C19.2, C20.C, C21.2, JP38.1, U7.7, U7.18, U7.21, U7.25, U7.26, X7.GND
GND7: C22.2, C23.C, C24.2, JP44.1, U8.7, U8.18, U8.21, U8.25, U8.26, X8.GND
GND8: C25.2, C26.C, C27.2, JP50.1, U9.7, U9.18, U9.21, U9.25, U9.26, X9.GND
GND9: C28.2, C29.C, C30.2, JP56.1, U10.7, U10.18, U10.21, U10.25, U10.26, X10.GND
GND10: C31.2, C32.C, C33.2, JP62.1, U11.7, U11.18, U11.21, U11.25, U11.26, X11.GND
GND11: C34.2, C35.C, C36.2, JP68.1, U12.7, U12.18, U12.21, U12.25, U12.26, X12.GND
GND12: C37.2, C38.C, C39.2, JP74.1, U13.7, U13.18, U13.21, U13.25, U13.26, X13.GND
GND13: C40.2, C41.C, C42.2, JP80.1, U14.7, U14.18, U14.21, U14.25, U14.26, X14.GND
GND14: C43.2, C44.C, C45.2, JP86.1, U15.7, U15.18, U15.21, U15.25, U15.26, X15.GND
GND15: C46.2, C47.C, C48.2, JP92.1, U16.7, U16.18, U16.21, U16.25, U16.26, X16.GND
GND16: C49.2, C50.C, C51.2, JP98.1, U17.7, U17.18, U17.21, U17.25, U17.26, X17.GND
GND17: C52.2, C53.C, C54.2, JP104.1, U18.7, U18.18, U18.21, U18.25, U18.26, X18.GND
GND18: C55.2, C56.C, C57.2, JP110.1, U19.7, U19.18, U19.21, U19.25, U19.26, X19.GND
GND19: C58.2, C59.C, C60.2, JP116.1, U20.7, U20.18, U20.21, U20.25, U20.26, X20.GND
GND20: C61.2, C62.C, C63.2, JP122.1, U21.7, U21.18, U21.21, U21.25, U21.26, X21.GND
GND21: C64.2, C65.C, C66.2, JP128.1, U22.7, U22.18, U22.21, U22.25, U22.26, X22.GND
GND22: C67.2, C68.C, C69.2, JP134.1, U23.7, U23.18, U23.21, U23.25, U23.26, X23.GND
GND23: C70.2, C71.C, C72.2, JP140.1, U24.7, U24.18, U24.21, U24.25, U24.26, X24.GND
GND24: C73.2, C74.C, C75.2, JP146.1, U25.7, U25.18, U25.21, U25.25, U25.26, X25.GND
GND25: C76.2, C77.C, C78.2, JP152.1, U26.7, U26.18, U26.21, U26.25, U26.26, X26.GND
GND26: C79.2, C80.C, C81.2, JP158.1, U27.7, U27.18, U27.21, U27.25, U27.26, X27.GND
GND27: C82.2, C83.C, C84.2, JP164.1, U28.7, U28.18, U28.21, U28.25, U28.26, X28.GND
GND28: C85.2, C86.C, C87.2, JP170.1, U29.7, U29.18, U29.21, U29.25, U29.26, X29.GND
GND29: C88.2, C89.C, C90.2, JP176.1, U30.7, U30.18, U30.21, U30.25, U30.26, X30.GND
GND30: C91.2, C92.C, C93.2, JP182.1, U31.7, U31.18, U31.21, U31.25, U31.26, X31.GND
GND31: C94.2, C95.C, C96.2, JP188.1, U32.7, U32.18, U32.21, U32.25, U32.26, X32.GND
GND32: C97.2, C98.C, C99.2, JP194.1, U33.7, U33.18, U33.21, U33.25, U33.26, X33.GND
GND33: C100.2, C101.C, C102.2, JP200.1, U34.7, U34.18, U34.21, U34.25, U34.26, X34.GND
GND34: C103.2, C104.C, C105.2, JP206.1, U35.7, U35.18, U35.21, U35.25, U35.26, X35.GND
GND35: C106.2, C107.C, C108.2, JP212.1, U36.7, U36.18, U36.21, U36.25, U36.26, X36.GND
GND36: C109.2, C110.C, C111.2, JP218.1, U37.7, U37.18, U37.21, U37.25, U37.26, X37.GND
GND37: C112.2, C113.C, C114.2, JP224.1, U38.7, U38.18, U38.21, U38.25, U38.26, X38.GND
GND38: C115.2, C116.C, C117.2, JP230.1, U39.7, U39.18, U39.21, U39.25, U39.26, X39.GND
GND39: C118.2, C119.C, C120.2, JP236.1, U40.7, U40.18, U40.21, U40.25, U40.26, X40.GND
GND40: C121.2, C122.C, C123.2, JP242.1, U41.7, U41.18, U41.21, U41.25, U41.26, X41.GND
GND41: C124.2, C125.C, C126.2, JP248.1, U42.7, U42.18, U42.21, U42.25, U42.26, X42.GND
GND42: C127.2, C128.C, C129.2, JP254.1, U43.7, U43.18, U43.21, U43.25, U43.26, X43.GND
GND43: C130.2, C131.C, C132.2, JP260.1, U44.7, U44.18, U44.21, U44.25, U44.26, X44.GND
GND44: C133.2, C134.C, C135.2, JP266.1, U45.7, U45.18, U45.21, U45.25, U45.26, X45.GND
GND45: C136.2, C137.C, C138.2, JP272.1, U46.7, U46.18, U46.21, U46.25, U46.26, X46.GND
GND46: C139.2, C140.C, C141.2, JP278.1, U47.7, U47.18, U47.21, U47.25, U47.26, X47.GND
GND47: C142.2, C143.C, C144.2, JP284.1, U48.7, U48.18, U48.21, U48.25, U48.26, X48.GND
GND48: C145.2, C146.C, C147.2, JP290.1, U49.7, U49.18, U49.21, U49.25, U49.26, X49.GND
GND49: C148.2, C149.C, C150.2, JP296.1, U50.7, U50.18, U50.21, U50.25, U50.26, X50.GND
GND50: C151.2, C152.C, C153.2, JP302.1, U51.7, U51.18, U51.21, U51.25, U51.26, X51.GND
GND51: C154.2, C155.C, C156.2, JP308.1, U52.7, U52.18, U52.21, U52.25, U52.26, X52.GND
GND52: C157.2, C158.C, C159.2, JP314.1, U53.7, U53.18, U53.21, U53.25, U53.26, X53.GND
GND53: C160.2, C161.C, C162.2, JP320.1, U54.7, U54.18, U54.21, U54.25, U54.26, X54.GND
GND54: C163.2, C164.C, C165.2, JP326.1, U55.7, U55.18, U55.21, U55.25, U55.26, X55.GND
GND55: C166.2, C167.C, C168.2, JP332.1, U56.7, U56.18, U56.21, U56.25, U56.26, X56.GND
GND56: C169.2, C170.C, C171.2, JP338.1, U57.7, U57.18, U57.21, U57.25, U57.26, X57.GND
GND57: C172.2, C173.C, C174.2, JP344.1, U58.7, U58.18, U58.21, U58.25, U58.26, X58.GND
GND58: C175.2, C176.C, C177.2, JP350.1, U59.7, U59.18, U59.21, U59.25, U59.26, X59.GND
GND59: C178.2, C179.C, C180.2, JP356.1, U60.7, U60.18, U60.21, U60.25, U60.26, X60.GND
GND60: C181.2, C182.C, C183.2, JP362.1, U61.7, U61.18, U61.21, U61.25, U61.26, X61.GND
GND61: C184.2, C185.C, C186.2, JP368.1, U62.7, U62.18, U62.21, U62.25, U62.26, X62.GND
GND62: C187.2, C188.C, C189.2, JP374.1, U63.7, U63.18, U63.21, U63.25, U63.26, X63.GND
GND63: C190.2, C191.C, C192.2, JP380.1, U64.7, U64.18, U64.21, U64.25, U64.26, X64.GND
GND64: C193.2, C194.C, C195.2, JP386.1, U65.7, U65.18, U65.21, U65.25, U65.26, X65.GND
GND65: C196.2, C197.C, C198.2, JP392.1, U66.7, U66.18, U66.21, U66.25, U66.26, X66.GND
GND66: C199.2, C200.C, C201.2, JP398.1, U67.7, U67.18, U67.21, U67.25, U67.26, X67.GND
GND67: C202.2, C203.C, C204.2, JP404.1, U68.7, U68.18, U68.21, U68.25, U68.26, X68.GND
GND68: C205.2, C206.C, C207.2, JP410.1, U69.7, U69.18, U69.21, U69.25, U69.26, X69.GND
GND69: C208.2, C209.C, C210.2, JP416.1, U70.7, U70.18, U70.21, U70.25, U70.26, X70.GND
GND70: C211.2, C212.C, C213.2, JP422.1, U71.7, U71.18, U71.21, U71.25, U71.26, X71.GND
GND71: C214.2, C215.C, C216.2, JP428.1, U72.7, U72.18, U72.21, U72.25, U72.26, X72.GND
GND72: C217.2, C218.C, C219.2, JP434.1, U73.7, U73.18, U73.21, U73.25, U73.26, X73.GND
GND73: C220.2, C221.C, C222.2, JP440.1, U74.7, U74.18, U74.21, U74.25, U74.26, X74.GND
GND74: C223.2, C224.C, C225.2, JP446.1, U75.7, U75.18, U75.21, U75.25, U75.26, X75.GND
GND75: C226.2, C227.C, C228.2, JP452.1, U76.7, U76.18, U76.21, U76.25, U76.26, X76.GND
GND76: C229.2, C230.C, C231.2, JP458.1, U77.7, U77.18, U77.21, U77.25, U77.26, X77.GND
GND77: C232.2, C233.C, C234.2, JP464.1, U78.7, U78.18, U78.21, U78.25, U78.26, X78.GND
GND78: C235.2, C236.C, C237.2, JP470.1, U79.7, U79.18, U79.21, U79.25, U79.26, X79.GND
GND79: C238.2, C239.C, C240.2, JP476.1, U80.7, U80.18, U80.21, U80.25, U80.26, X80.GND
GND80: C241.2, C242.C, C243.2, JP482.1, U81.7, U81.18, U81.21, U81.25, U81.26, X81.GND
GND81: C244.2, C245.C, C246.2, JP488.1, U82.7, U82.18, U82.21, U82.25, U82.26, X82.GND
GND82: C247.2, C248.C, C249.2, JP494.1, U83.7, U83.18, U83.21, U83.25, U83.26, X83.GND
GND83: C250.2, C251.C, C252.2, JP500.1, U84.7, U84.18, U84.21, U84.25, U84.26, X84.GND
GND84: C253.2, C254.C, C255.2, JP506.1, U85.7, U85.18, U85.21, U85.25, U85.26, X85.GND
GND85: C256.2, C257.C, C258.2, JP512.1, U86.7, U86.18, U86.21, U86.25, U86.26, X86.GND
GND86: C259.2, C260.C, C261.2, JP518.1, U87.7, U87.18, U87.21, U87.25, U87.26, X87.GND
GND87: C262.2, C263.C, C264.2, JP524.1, U88.7, U88.18, U88.21, U88.25, U88.26, X88.GND
GND88: C265.2, C266.C, C267.2, JP530.1, U89.7, U89.18, U89.21, U89.25, U89.26, X89.GND
GND89: C268.2, C269.C, C270.2, JP536.1, U90.7, U90.18, U90.21, U90.25, U90.26, X90.GND
GND90: C271.2, C272.C, C273.2, JP542.1, U91.7, U91.18, U91.21, U91.25, U91.26, X91.GND
GND91: C274.2, C275.C, C276.2, JP548.1, U92.7, U92.18, U92.21, U92.25, U92.26, X92.GND
GND92: C277.2, C278.C, C279.2, JP554.1, U93.7, U93.18, U93.21, U93.25, U93.26, X93.GND
GND93: C280.2, C281.C, C282.2, JP560.1, U94.7, U94.18, U94.21, U94.25, U94.26, X94.GND
GND94: C283.2, C284.C, C285.2, JP566.1, U95.7, U95.18, U95.21, U95.25, U95.26, X95.GND
GND95: C286.2, C287.C, C288.2, JP572.1, U96.7, U96.18, U96.21, U96.25, U96.26, X96.GND
GND96: C289.2, C290.C, C291.2, JP578.1, U97.7, U97.18, U97.21, U97.25, U97.26, X97.GND
GND97: C292.2, C293.C, C294.2, JP584.1, U98.7, U98.18, U98.21, U98.25, U98.26, X98.GND
GND98: C295.2, C296.C, C297.2, JP590.1, U99.7, U99.18, U99.21, U99.25, U99.26, X99.GND
GND99: C298.2, C299.C, C300.2, JP596.1, U100.7, U100.18, U100.21, U100.25, U100.26, X100.GND
unnamed: LED1.A, R1.1
unnamed: LED2.A, R2.1
unnamed: LED3.A, R3.1
unnamed: LED4.A, R4.1
unnamed: LED5.A, R5.1
unnamed: LED6.A, R6.1
unnamed: LED7.A, R7.1
unnamed: LED8.A, R8.1
unnamed: LED9.A, R9.1
unnamed: LED10.A, R10.1
unnamed: LED11.A, R11.1
unnamed: LED12.A, R12.1
unnamed: LED13.A, R13.1
unnamed: LED14.A, R14.1
unnamed: LED15.A, R15.1
unnamed: LED16.A, R16.1
unnamed: LED17.A, R17.1
unnamed: LED18.A, R18.1
unnamed: LED19.A, R19.1
unnamed: LED20.A, R20.1
unnamed: LED21.A, R21.1
unnamed: LED22.A, R22.1
unnamed: LED23.A, R23.1
unnamed: LED24.A, R24.1
unnamed: LED25.A, R25.1
unnamed: LED26.A, R26.1
unnamed: LED27.A, R27.1
unnamed: LED28.A, R28.1
unnamed: LED29.A, R29.1
unnamed: LED30.A, R30.1
unnamed: LED31.A, R31.1
unnamed: LED32.A, R32.1
unnamed: LED33.A, R33.1
unnamed: LED34.A, R34.1
unnamed: LED35.A, R35.1
unnamed: LED36.A, R36.1
unnamed: LED37.A, R37.1
unnamed: LED38.A, R38.1
unnamed: LED39.A, R39.1
unnamed: LED40.A, R40.1
unnamed: LED41.A, R41.1
unnamed: LED42.A, R42.1
unnamed: LED43.A, R43.1
unnamed: LED44.A, R44.1
unnamed: LED45.A, R45.1
unnamed: LED46.A, R46.1
unnamed: LED47.A, R47.1
unnamed: LED48.A, R48.1
unnamed: LED49.A, R49.1
unnamed: LED50.A, R50.1
unnamed: LED51.A, R51.1
unnamed: LED52.A, R52.1
unnamed: LED53.A, R53.1
unnamed: LED54.A, R54.1
unnamed: LED55.A, R55.1
unnamed: LED56.A, R56.1
unnamed: LED57.A, R57.1
unnamed: LED58.A, R58.1
unnamed: LED59.A, R59.1
unnamed: LED60.A, R60.1
unnamed: LED61.A, R61.1
unnamed: LED62.A, R62.1
unnamed: LED63.A, R63.1
unnamed: LED64.A, R64.1
unnamed: LED65.A, R65.1
unnamed: LED66.A, R66.1
unnamed: LED67.A, R67.1
unnamed: LED68.A, R68.1
unnamed: LED69.A, R69.1
unnamed: LED70.A, R70.1
unnamed: LED71.A, R71.1
unnamed: LED72.A, R72.1
unnamed: LED73.A, R73.1
unnamed: LED74.A, R74.1
unnamed: LED75.A, R75.1
unnamed: LED76.A, R76.1
unnamed: LED77.A, R77.1
unnamed: LED78.A, R78.1
unnamed: LED79.A, R79.1
unnamed: LED80.A, R80.1
unnamed: LED81.A, R81.1
unnamed: LED82.A, R82.1
unnamed: LED83.A, R83.1
unnamed: LED84.A, R84.1
unnamed: LED85.A, R85.1
unnamed: LED86.A, R86.1
unnamed: LED87.A, R87.1
unnamed: LED88.A, R88.1
unnamed: LED89.A, R89.1
unnamed: LED90.A, R90.1
unnamed: LED91.A, R91.1
unnamed: LED92.A, R92.1
unnamed: LED93.A, R93.1
unnamed: LED94.A, R94.1
unnamed: LED95.A, R95.1
unnamed: LED96.A, R96.1
unnamed: LED97.A, R97.1
unnamed: LED98.A, R98.1
unnamed: LED99.A, R99.1
unnamed: LED100.A, R100.1
unnamed: LED101.A, R101.1
unnamed: LED102.A, R102.1
unnamed: LED103.A, R103.1
unnamed: LED104.A, R104.1
unnamed: LED105.A, R105.1
unnamed: LED106.A, R106.1
unnamed: LED107.A, R107.1
unnamed: LED108.A, R108.1
unnamed: LED109.A, R109.1
unnamed: LED110.A, R110.1
unnamed: LED111.A, R111.1
unnamed: LED112.A, R112.1
unnamed: LED113.A, R113.1
unnamed: LED114.A, R114.1
unnamed: LED115.A, R115.1
unnamed: LED116.A, R116.1
unnamed: LED117.A, R117.1
unnamed: LED118.A, R118.1
unnamed: LED119.A, R119.1
unnamed: LED120.A, R120.1
unnamed: LED121.A, R121.1
unnamed: LED122.A, R122.1
unnamed: LED123.A, R123.1
unnamed: LED124.A, R124.1
unnamed: LED125.A, R125.1
unnamed: LED126.A, R126.1
unnamed: LED127.A, R127.1
unnamed: LED128.A, R128.1
unnamed: LED129.A, R129.1
unnamed: LED130.A, R130.1
unnamed: LED131.A, R131.1
unnamed: LED132.A, R132.1
unnamed: LED133.A, R133.1
unnamed: LED134.A, R134.1
unnamed: LED135.A, R135.1
unnamed: LED136.A, R136.1
unnamed: LED137.A, R137.1
unnamed: LED138.A, R138.1
unnamed: LED139.A, R139.1
unnamed: LED140.A, R140.1
unnamed: LED141.A, R141.1
unnamed: LED142.A, R142.1
unnamed: LED143.A, R143.1
unnamed: LED144.A, R144.1
unnamed: LED145.A, R145.1
unnamed: LED146.A, R146.1
unnamed: LED147.A, R147.1
unnamed: LED148.A, R148.1
unnamed: LED149.A, R149.1
unnamed: LED150.A, R150.1
unnamed: LED151.A, R151.1
unnamed: LED152.A, R152.1
unnamed: LED153.A, R153.1
unnamed: LED154.A, R154.1
unnamed: LED155.A, R155.1
unnamed: LED156.A, R156.1
unnamed: LED157.A, R157.1
unnamed: LED158.A, R158.1
unnamed: LED159.A, R159.1
unnamed: LED160.A, R160.1
unnamed: LED161.A, R161.1
unnamed: LED162.A, R162.1
unnamed: LED163.A, R163.1
unnamed: LED164.A, R164.1
unnamed: LED165.A, R165.1
unnamed: LED166.A, R166.1
unnamed: LED167.A, R167.1
unnamed: LED168.A, R168.1
unnamed: LED169.A, R169.1
unnamed: LED170.A, R170.1
unnamed: LED171.A, R171.1
unnamed: LED172.A, R172.1
unnamed: LED173.A, R173.1
unnamed: LED174.A, R174.1
unnamed: LED175.A, R175.1
unnamed: LED176.A, R176.1
unnamed: LED177.A, R177.1
unnamed: LED178.A, R178.1
unnamed: LED179.A, R179.1
unnamed: LED180.A, R180.1
unnamed: LED181.A, R181.1
unnamed: LED182.A, R182.1
unnamed: LED183.A, R183.1
unnamed: LED184.A, R184.1
unnamed: LED185.A, R185.1
unnamed: LED186.A, R186.1
unnamed: LED187.A, R187.1
unnamed: LED188.A, R188.1
unnamed: LED189.A, R189.1
unnamed: LED190.A, R190.1
unnamed: LED191.A, R191.1
unnamed: LED192.A, R192.1
unnamed: LED193.A, R193.1
unnamed: LED194.A, R194.1
unnamed: LED195.A, R195.1
unnamed: LED196.A, R196.1
unnamed: LED197.A, R197.1
unnamed: LED198.A, R198.1
unnamed: LED199.A, R199.1
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
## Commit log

2013-06-03 Adding board files and updating README
2013-06-03 Update README.md
    Fixed formatting for Repo Contents
2013-06-10 Adding Giant Panel files for production
    This is the giant panel for the MYDATA pick and place machine.
2013-06-10 Adding Giant Panel for 5V version
2013-06-10 Organized folder structure
2015-02-05 Fixing repo to only reflect 5V FTDI board files
2015-02-05 Fixing README typo
2015-04-20 recreated panel for machine optimization
